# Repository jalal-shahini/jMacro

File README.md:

# jMacro
## A Custom Built Macro Keyboard

This is a macro keyboard I designed to be:

1. a Numpad once a month when I need one.
2. an easy way to type the special characters I use constantly when taking notes such as ※, ℍ, Ω, ℚ, ∵, ∴, ℘ etc.
3. a life-saver when playing games.

The keyboard uses an Atmega32u4 microcontroller.
It features 22 keys with two rotary encoders with a Schmitt-trigger for a clean signal.

### To Do for a Future Version

* Single LED indicator is too bright and not ideal. I will use backlight LEDs for each individual key.
* Rotary encoders and USB circuit will benefit from a 4 layer PCB.
* Switches are better to be hot swappable.
* The electolytic capacitors are THT to save costs, however, in the next versions it is better to use all SMD components.

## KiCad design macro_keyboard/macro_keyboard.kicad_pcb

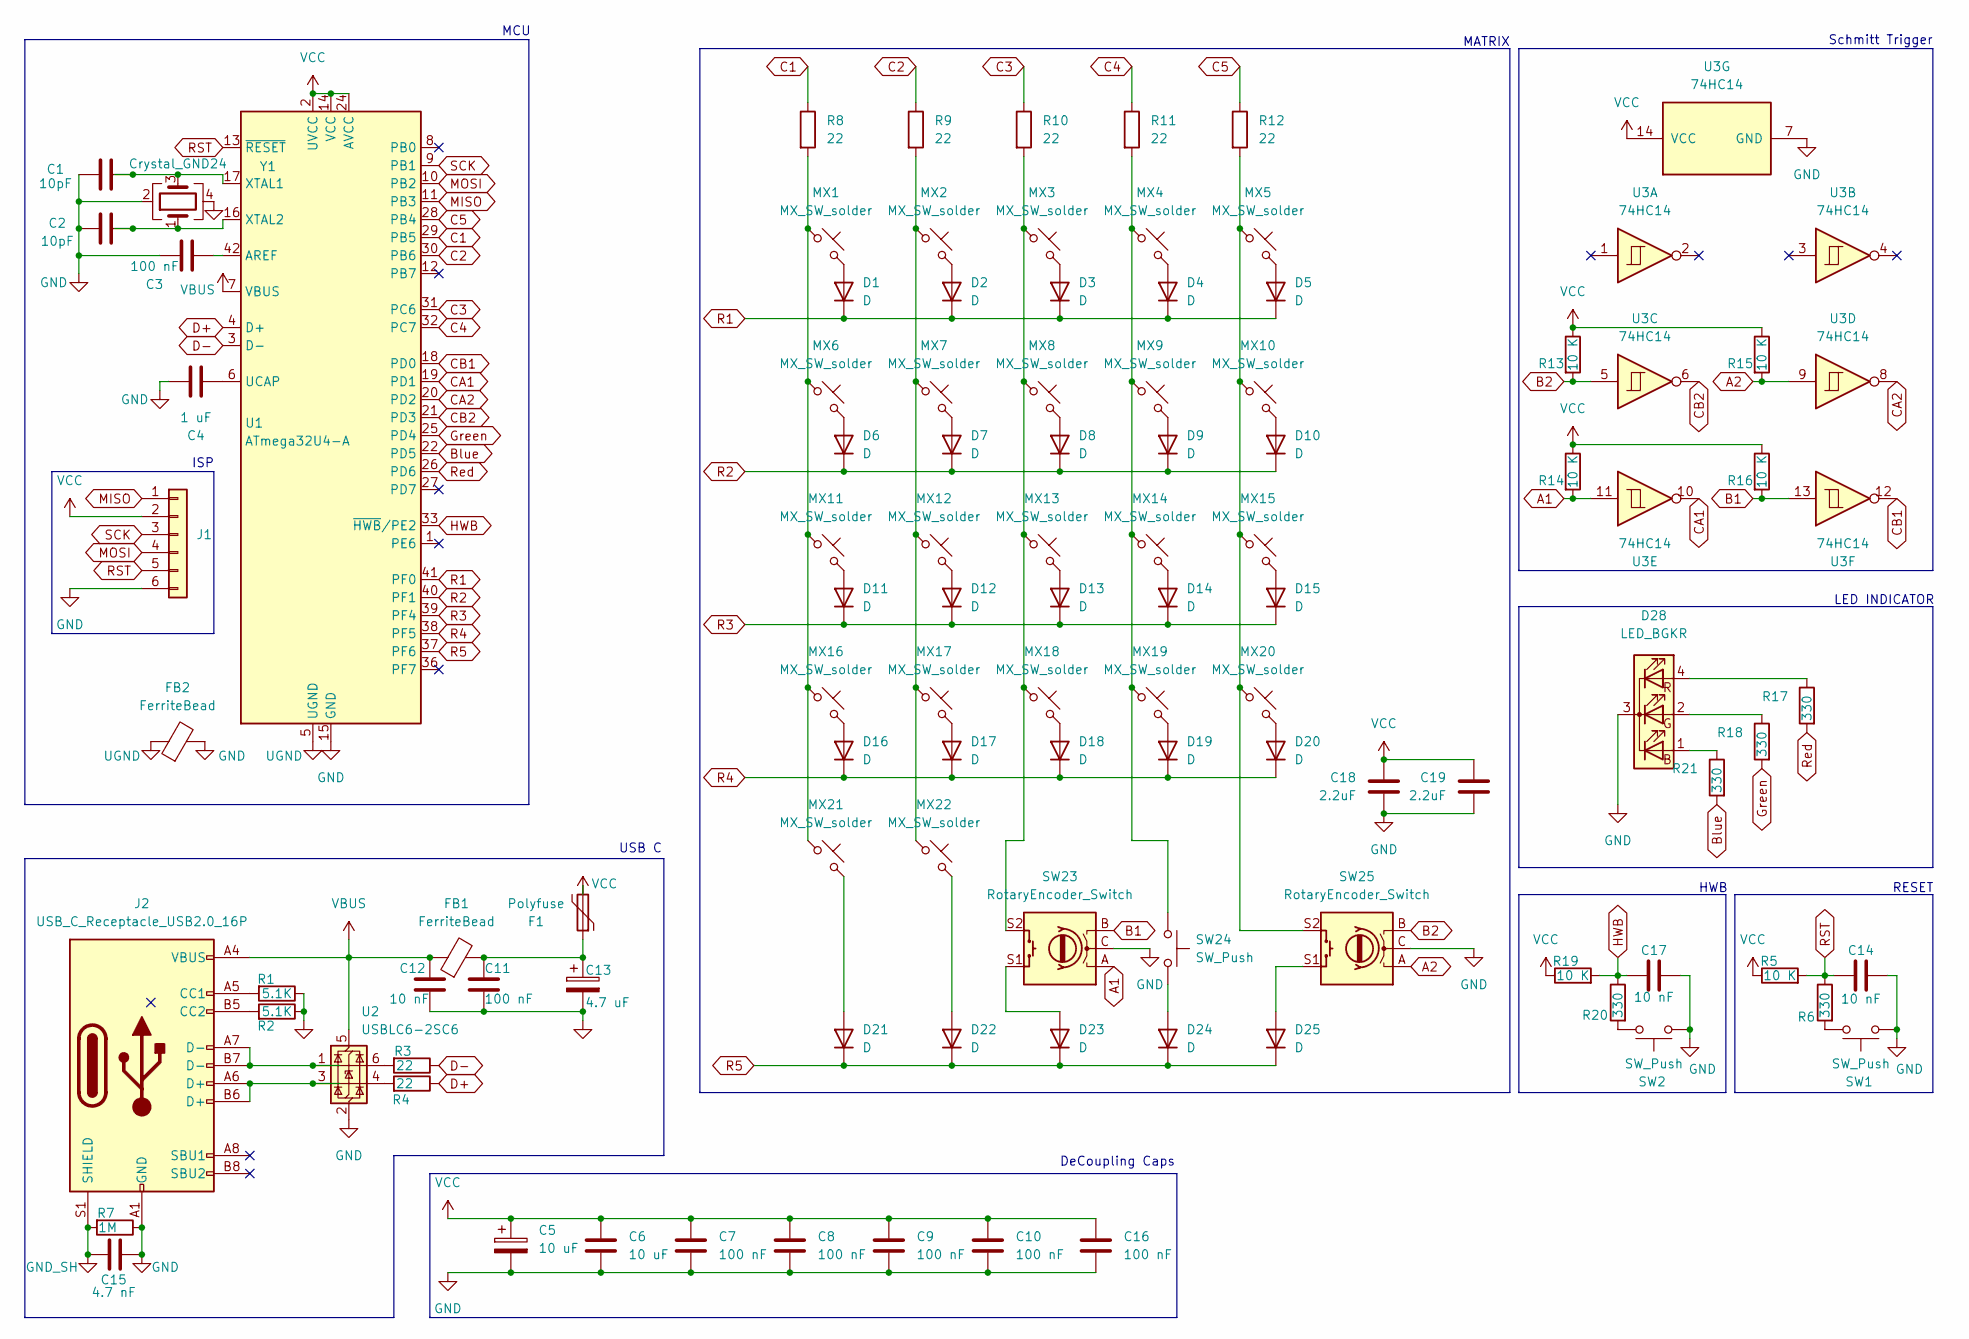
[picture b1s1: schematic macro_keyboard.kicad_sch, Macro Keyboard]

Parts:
C1, C2: 10pF; C_0402_1005Metric; LCSC C32949
C3, C7, C8, C9, C10, C11, C16: 100 nF; C_0402_1005Metric; LCSC C1525
C4: 1 uF; C_0402_1005Metric; LCSC C52923
C5: 10 uF; CP_Radial_D4.0mm_P2.00mm
C6: 10 uF; C_0402_1005Metric; LCSC C15525
C12, C14, C17: 10 nF; C_0402_1005Metric; LCSC C15195
C13: 4.7 uF; CP_Radial_D4.0mm_P2.00mm
C15: 4.7 nF; C_0402_1005Metric; LCSC C1538
C18, C19: 2.2uF; C_0402_1005Metric; LCSC C12530
D1, D2, D3, D4, D5, D6, D7, D8, D9, D10, D11, D12, D13, D14, D15, D16, D17, D18, D19, D20, D21, D22, D23, D24, D25: D; D_SOD-323; LCSC C2128
D28: LED_BGKR; LED_D5.0mm-4_RGB
F1: Polyfuse; Fuse_1812_4532Metric; LCSC C3102
FB1: FerriteBead; BEADC1608X95N; LCSC C14709
FB2: FerriteBead; C_0603_1608Metric; LCSC C14709
J1: Conn_01x06; PinHeader_2x03_P2.54mm_Vertical
J2: USB_C_Receptacle_USB2.0_16P; USB_C_Receptacle_HCTL_HC-TYPE-C-16P-01A; LCSC C2894897
MX1, MX2, MX3, MX4, MX5, MX6, MX7, MX8, MX9, MX10, MX11, MX12, MX13, MX14, MX15, MX16, MX17, MX18, MX19, MX20, MX21, MX22: MX_SW_solder; SW_Cherry_MX_Plate_1.00u
R1, R2: 5.1K; R_0402_1005Metric; LCSC C25905
R3, R4, R8, R9, R10, R11, R12: 22; R_0402_1005Metric; LCSC C25092
R5, R13, R14, R15, R16, R19: 10 K; R_0402_1005Metric; LCSC C25744
R6, R17, R18, R20, R21: 330; R_0402_1005Metric; LCSC C25104
R7: 1M; R_0402_1005Metric; LCSC C26083
SW1: SW_Push; SW_PUSH_6mm_H4.3mm
SW2: SW_Push; SW_Push_1P1T_XKB_TS-1187A; LCSC C318884
SW23, SW25: RotaryEncoder_Switch; RotaryEncoder_Alps_EC11E-Switch_Vertical_H20mm
SW24: SW_Push; SW_PUSH_6mm_H9.5mm
U1: ATmega32U4-A; TQFP-44_10x10mm_P0.8mm; LCSC C2052746
U2: USBLC6-2SC6; SOT-23-6; LCSC C7519
U3: 74HC14; SOIC-14_3.9x8.7mm_P1.27mm; LCSC C5605
Y1: Crystal_GND24; OSC_X322516MLB4SI; LCSC C13738

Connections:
A1: R14.2, SW23.A, U3.11
A2: R15.2, SW25.A, U3.9
B1: R16.2, SW23.B, U3.13
B2: R13.2, SW25.B, U3.5
Blue: R21.2, U1.22 (PD5)
C1: R8.1, U1.29 (PB5)
C2: R9.1, U1.30 (PB6)
C3: R10.1, U1.31 (PC6)
C4: R11.1, U1.32 (PC7)
C5: R12.1, U1.28 (PB4)
CA1: U1.19 (PD1), U3.10
CA2: U1.20 (PD2), U3.8
CB1: U1.18 (PD0), U3.12
CB2: U1.21 (PD3), U3.6
D+: R4.1, U1.4 (D+)
D-: R3.1, U1.3 (D-)
GND: C1.1, C2.1, C3.1, C4.2, C5.2, C6.2, C7.2, C8.2, C9.2, C10.2, C11.2, C12.2, C13.2, C14.2, C15.2, C16.2, C17.2, C18.2, C19.2, D28.3 (K), FB2.2, J1.6, J2.A1 (GND), J2.A12 (GND), J2.B1 (GND), J2.B12 (GND), R1.1, R2.1, R7.1, SW1.2, SW2.2, SW23.C, SW25.C, U1.15 (GND), U1.23 (GND), U1.35 (GND), U1.43 (GND), U2.2 (GND), U3.7 (GND), Y1.2, Y1.4
GND_SH: C15.1, J2.S1 (SHIELD), R7.2
Green: R18.2, U1.25 (PD4)
HWB: C17.1, R19.2, R20.1, U1.33 (~HWB/PE2)
MISO: J1.1, U1.11 (PB3)
MOSI: J1.4, U1.10 (PB2)
unnamed: C11.1, C13.1, F1.1, FB1.2
unnamed: D1.2 (A), MX1.2
unnamed: D2.2 (A), MX2.2
unnamed: D3.2 (A), MX3.2
unnamed: D4.2 (A), MX4.2
unnamed: D5.2 (A), MX5.2
unnamed: D6.2 (A), MX6.2
unnamed: D7.2 (A), MX7.2
unnamed: D8.2 (A), MX8.2
unnamed: D9.2 (A), MX9.2
unnamed: D10.2 (A), MX10.2
unnamed: D11.2 (A), MX11.2
unnamed: D12.2 (A), MX12.2
unnamed: D13.2 (A), MX13.2
unnamed: D14.2 (A), MX14.2
unnamed: D15.2 (A), MX15.2
unnamed: D16.2 (A), MX16.2
unnamed: D17.2 (A), MX17.2
unnamed: D18.2 (A), MX18.2
unnamed: D19.2 (A), MX19.2
unnamed: D20.2 (A), MX20.2
unnamed: D21.2 (A), MX21.2
unnamed: D22.2 (A), MX22.2
unnamed: D23.2 (A), SW23.S1
unnamed: D24.2 (A), SW24.2
unnamed: D25.2 (A), SW25.S1
unnamed: D28.1 (BA), R21.1
unnamed: D28.2 (GA), R18.1
unnamed: D28.4 (RA), R17.1
unnamed: J2.A5 (CC1), R1.2
unnamed: J2.B5 (CC2), R2.2
unnamed: J2.A6 (D+), J2.B6 (D+), U2.3 (I/O2)
unnamed: J2.A7 (D-), J2.B7 (D-), U2.1 (I/O1)
unnamed: MX1.1, MX6.1, MX11.1, MX16.1, MX21.1, R8.2
unnamed: MX5.1, MX10.1, MX15.1, MX20.1, R12.2, SW25.S2
unnamed: MX2.1, MX7.1, MX12.1, MX17.1, MX22.1, R9.2
unnamed: MX3.1, MX8.1, MX13.1, MX18.1, R10.2, SW23.S2
unnamed: MX4.1, MX9.1, MX14.1, MX19.1, R11.2, SW24.1
unnamed: R3.2, U2.6 (I/O1)
unnamed: R4.2, U2.4 (I/O2)
unnamed: R6.2, SW1.1
unnamed: R20.2, SW2.1
unnamed: C3.2, U1.42 (AREF)
unnamed: C4.1, U1.6 (UCAP)
unnamed: C1.2, U1.17 (XTAL1), Y1.3
unnamed: C2.2, U1.16 (XTAL2), Y1.1
R1: D1.1 (K), D2.1 (K), D3.1 (K), D4.1 (K), D5.1 (K), U1.41 (PF0)
R2: D6.1 (K), D7.1 (K), D8.1 (K), D9.1 (K), D10.1 (K), U1.40 (PF1)
R3: D11.1 (K), D12.1 (K), D13.1 (K), D14.1 (K), D15.1 (K), U1.39 (PF4)
R4: D16.1 (K), D17.1 (K), D18.1 (K), D19.1 (K), D20.1 (K), U1.38 (PF5)
R5: D21.1 (K), D22.1 (K), D23.1 (K), D24.1 (K), D25.1 (K), U1.37 (PF6)
RST: C14.1, J1.5, R5.2, R6.1, U1.13 (~RESET)
Red: R17.2, U1.26 (PD6)
SCK: J1.3, U1.9 (PB1)
UGND: FB2.1, U1.5 (UGND)
VBUS: C12.1, FB1.1, J2.A4 (VBUS), J2.A9 (VBUS), J2.B4 (VBUS), J2.B9 (VBUS), U1.7 (VBUS), U2.5 (VBUS)
VCC: C5.1, C6.1, C7.1, C8.1, C9.1, C10.1, C16.1, C18.1, C19.1, F1.2, J1.2, R5.1, R13.1, R14.1, R15.1, R16.1, R19.1, U1.2 (UVCC), U1.14 (VCC), U1.24 (AVCC), U1.34 (VCC), U1.44 (AVCC), U3.14 (VCC)

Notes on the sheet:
RESET
HWB
DeCoupling Caps
ISP
USB C
MATRIX
MCU
Schmitt Trigger
LED INDICATOR

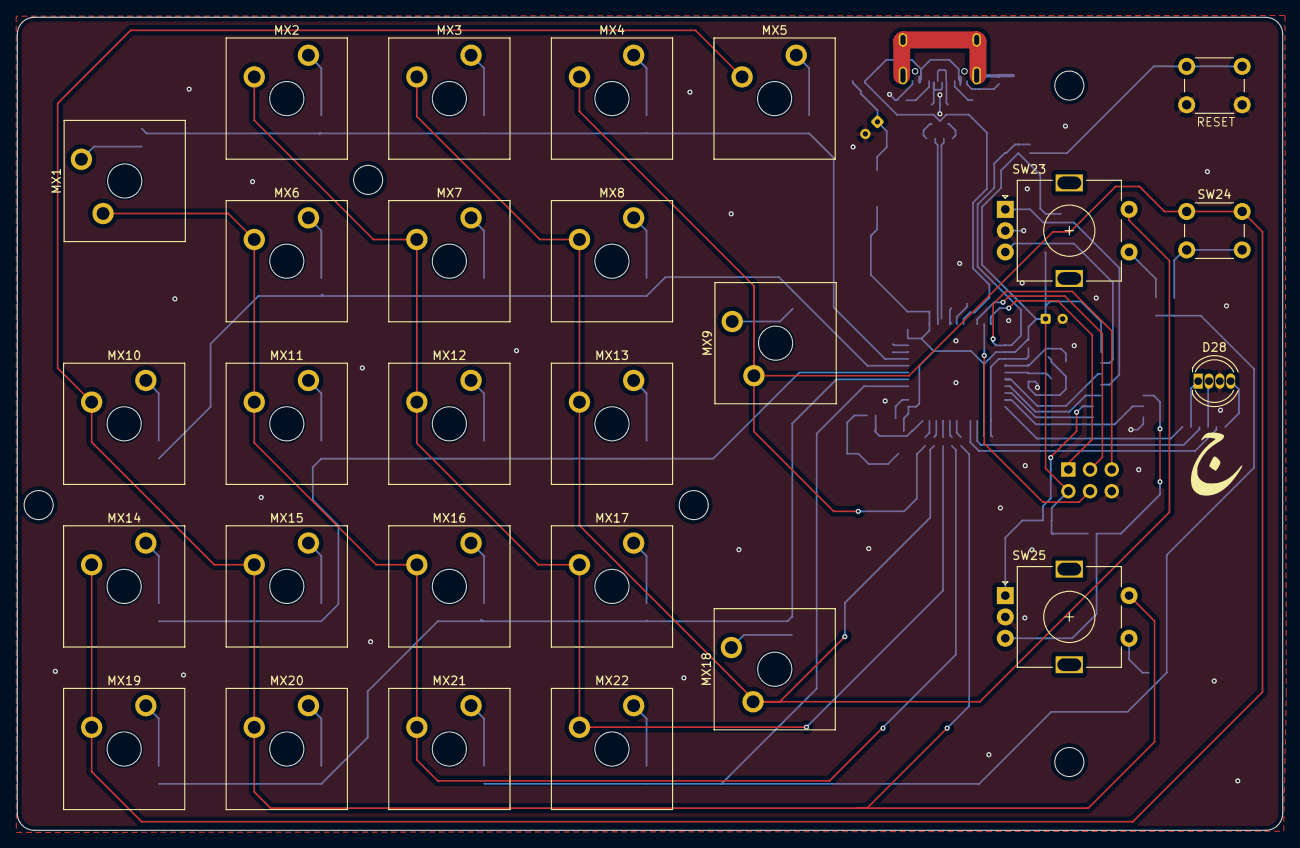
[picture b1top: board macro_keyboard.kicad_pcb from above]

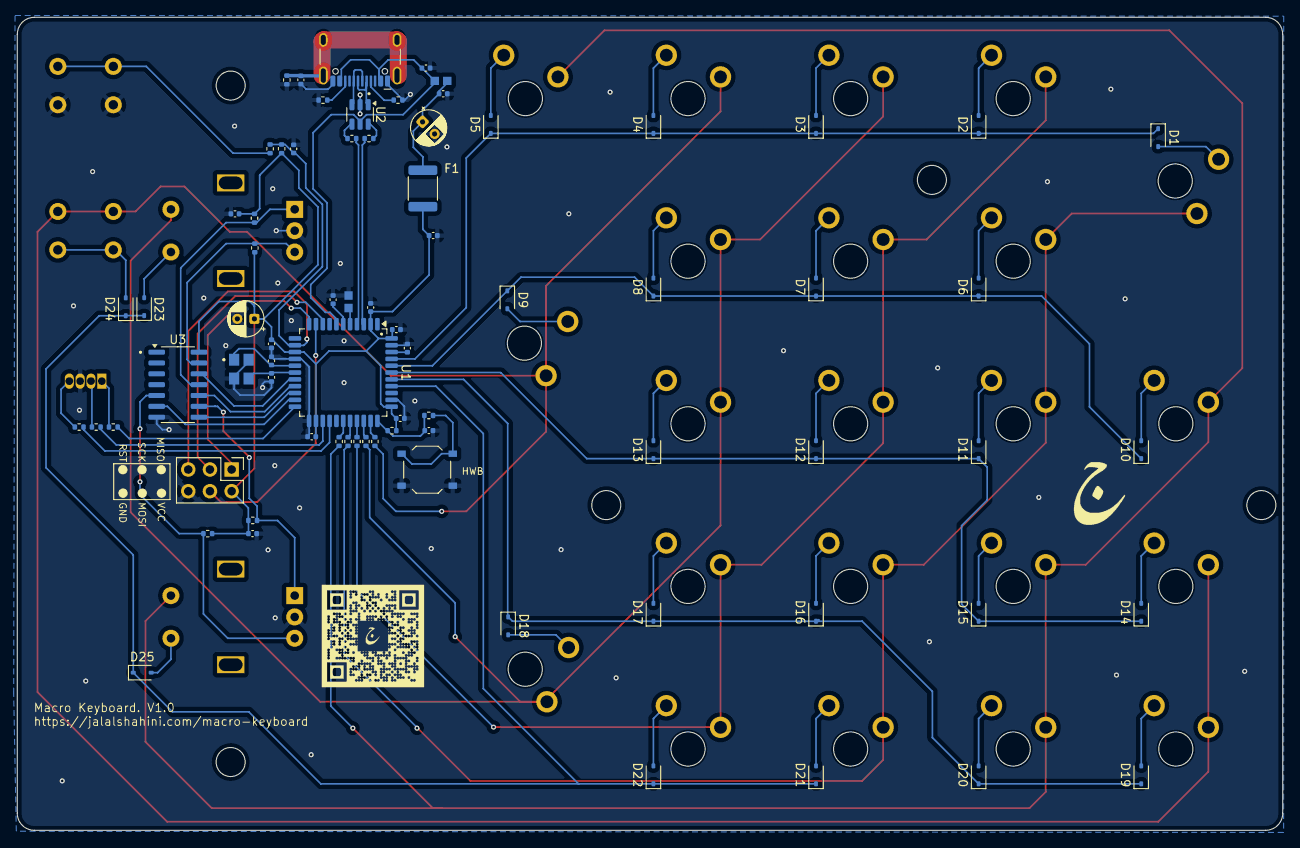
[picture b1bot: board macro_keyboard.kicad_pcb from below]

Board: 2 copper layers, 148.3 x 95.3 mm, 102 parts (75 on the bottom side), 79 nets.

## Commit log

2025-11-08 version 1.0
2025-11-09 encoder layer function
